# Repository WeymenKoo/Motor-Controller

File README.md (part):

# this written by claude yeh

Technical notes from a full design cycle: idea → theory → schematic → simulation → layout → fab → bring-up plan. Written as a knowledge refresher as much as a build log, so each section starts with the background needed to follow the decision.

**Status:** Rev 1 design-frozen, fabricated and partly bench-validated on a 12 V supply: MCU, gate driver (SPI), current sensing and PWM verified; a T-Motor MN601-S identified (R, L, back-EMF) and spun open-loop up to 1000 rpm. Not yet tested on the 12S bus, under load, or in closed-loop FOC. The design notes below are analytical or derived from the fabrication files.

## Repository layout

| Path | Contents |
|---|---|
| `FoC Motor Controller.kicad_pro` / `.kicad_sch` / `.kicad_pcb` | KiCad 10 project, root sheet and board |
| `Schematics/` | Hierarchical sheets (power, MCU, gate driver, MOSFETs, sensing, CAN-FD, interconnects, ...) |
| `Libraries/` | Project-local symbols, footprints and 3D models (referenced via `${KIPRJMOD}/Libraries/`) |
| `Documentation/` | Design rationale, layout/manufacturing review, board renders, RevC action summary |
| `Simulation/` | LTspice bench-correlation suite (hot-plug, half-bridge switching, current sense) with DHO804 bench captures and comparisons; see `Simulation/README.md` |
| `Project Outputs/` | BOM, pick-and-place, netlist, fabrication package (Rev 1), schematic PDF |

Open `FoC Motor Controller.kicad_pro` in KiCad 10. Vendor datasheets and the KiCad worksheet templates are not included in this repo; without the templates KiCad falls back to its default title block.

---

## 1. What and why

A single-axis field-oriented-control motor controller for one joint of a cat-scale bipedal robot. Six boards, one per joint, sharing a 12S bus, coordinated over CAN-FD.

The actuator architecture is **quasi-direct drive** — a low gear ratio (roughly 6:1 to 10:1) between a large-diameter pancake outrunner and the joint, rather than the 100:1+ of a conventional servo.

Why that matters, because it drives everything downstream:

| QDD property | Consequence for the electronics |
|---|---|
| Backdrivable, low reflected inertia | Torque control fidelity matters more than peak power. Current-sense accuracy becomes a first-class requirement, not an afterthought. |
| Joint torque ∝ motor current, almost directly | Current sense error *is* torque error. No gearbox to hide it behind. |
| Impacts transmit straight back to the motor | Regeneration is routine, not exceptional. Bus transient behaviour is a safety question. |
| It hangs on a limb | Board mass is a real constraint. An over-specified power stage is a defect, not free margin. |

Reference motor: ODrive M8325s, 100 KV, 92 mm pancake outrunner, **20 pole pairs**. That pole count comes back repeatedly.

---

## 2. Theory refresher: why FOC at all

### 2.1 The problem with six-step commutation

Trapezoidal (six-step) BLDC control energises two phases at a time and commutates on Hall transitions. It's simple, and for a fan or a drill it's fine. It has two properties that kill it for a leg joint:

- **Torque ripple.** Torque varies by roughly 13% across each 60° electrical sector because the current vector jumps in discrete steps rather than rotating smoothly.
- **No control of the current *angle*.** You can only control magnitude.

### 2.2 What FOC actually does

FOC transforms the three phase currents into a rotating reference frame locked to the rotor, so that a spinning three-phase AC problem becomes two DC quantities you can put a PI loop around.

```
Clarke:  3-phase (a,b,c)  →  2-axis stationary (α,β)
Park:    stationary (α,β) →  rotor-synchronous (d,q)   [needs rotor angle θ]

  i_d  = flux-producing current   → command 0 for a surface-PM motor
  i_q  = torque-producing current → this is your torque command
```

Two consequences worth internalising:

1. **Park needs θ.** The whole scheme collapses without an accurate rotor angle. This is why position sensing is not a peripheral feature — it is load-bearing.
2. **Commanding `i_d = 0`** means all current produces torque and none produces useless flux. That's the efficiency win over six-step, alongside the smoothness win.

The inverse path (inverse Park → SVM → gate signals) synthesises the voltage vector. **Space Vector Modulation** is worth knowing as the standard choice: it uses the two adjacent active vectors plus zero vectors, and by injecting a common-mode third harmonic it gets ~15% more bus utilisation than sinusoidal PWM for the same DC link.

### 2.3 Why sensorless was ruled out immediately

Sensorless FOC estimates θ from back-EMF. Back-EMF is proportional to speed, so at zero speed there is nothing to observe. A leg joint's primary duty is **holding position and torque at or near zero speed** — exactly where the observer has no signal.

Not a close call. Absolute magnetic encoder, AS5047P, 14-bit, over SPI.

**Refresher — magnetic encoder basics:** a diametrically-magnetised magnet on the shaft end, Hall array on the IC, sensing field *direction* not strength. Field strength only has to be in range (typically 30–70 mT). Absolute means it knows the angle at power-up with no homing move — essential when powering up a leg that is already loaded.

---

## 3. Requirements, and one I got wrong in my own documentation

```
Bus:              12S LiPo — 50.4 V full charge, 44.4 V nominal, 56 V max
Phase current:    10 A RMS continuous
Control:          sensored FOC, three-shunt low-side sensing
Comms:            CAN-FD, 6 nodes on a shared bus
Switching:        inaudible
```

### The f_sw story — worth reading as a lesson in post-hoc rationalisation

**The actual requirement was "inaudible."** 40 kHz was chosen as arbitrary headroom above the ~20 kHz audibility limit. That's it.

Later documentation in this project (including my own design record) presented a derivation:

```
f_electrical = rpm/60 × pole_pairs = 3500/60 × 20 ≈ 1167 Hz
20 PWM cycles per electrical cycle → ~23 kHz floor
∴ 40 kHz
```

That derivation is *correct arithmetic* and a genuinely useful sanity check — it confirms 40 kHz is comfortably above the control-bandwidth floor. But it is **not why the number was chosen**, and writing it up as though it were makes the design look more derived than it was.

Worth flagging because this is a common failure mode in engineering documentation: a number picked by judgement acquires a derivation after the fact, and three revisions later nobody remembers which constraint is real. If f_sw ever needs to move, the binding constraint is audibility and the charge-pump budget — not the pole-pair math.

**The 20-cycles-per-electrical-cycle rule** is still worth knowing: it's a sampling-rate argument. Your current loop runs at f_sw, and it has to track a sinusoid at f_electrical. Fewer than ~10–20 samples per cycle and the loop can't keep up with the rotating vector.

---

## 4. Design workflow

Fixed order, applied per subsystem:

```
1. First principles      → napkin numbers, identify the BINDING constraint
                           (no optimisation — the goal is order of magnitude)
2. SPICE                 → build from the napkin result, optimise here
3. Component search      → real parts, availability checked before committing
4. Power & thermal       → hot Rds(on), not the 25 °C headline
5. BoM consolidation     → once the design is stable, never during
6. Schematic review      → verify earlier action items actually landed
7. Layout
```

### Why LTspice is not used for the control loop

Tried it, abandoned it. The timescale separation is fatal:

```
Device switching:      ~5 ns edges
Mechanical settling:   ~500 ms
Ratio:                 10^8
```

A transient solver forced to resolve nanosecond edges across a mechanical settling time isn't just slow — it accumulates numerical error that swamps the result. **Control loops belong in discrete-time simulation. SPICE is for the power stage only.**

Three benches that were useful:

- `dpt_halfbridge.cir` — double-pulse test, one half-bridge
- `input_stage_transients.cir` — hot-plug and inductive transient
- `bus_regen_cascade.cir` — multi-board shared-bus regeneration

**Refresher — the double-pulse test (DPT)** is the standard method for characterising switching loss and overshoot. Two gate pulses: the first builds current in an inductive load, the gap measures turn-off, the second measures turn-on with the current already established. It isolates switching behaviour from conduction behaviour.

The single most useful result from the whole simulation effort:

```
Commutation loop inductance → V_GS undershoot
   2 nH  →  ~0 V
  80 nH  →  −4.9 V
```

Gate-oxide stress and false turn-off appear **well before** drain overshoot looks alarming on a scope. That reframed loop area as the number one layout variable, not one of several.

---

## 5. Power stage

### 5.1 Refresher: where the losses come from

```
Conduction:   P = I²_rms × R_DS(on, hot)
Switching:    P = ½ × V_bus × I × (t_r + t_f) × f_sw
```

Two things that trip people up:

**R_DS(on) roughly doubles from 25 °C to 150 °C.** The datasheet headline is at 25 °C. Using it for thermal work underestimates conduction loss by 2×.

**t_r and t_f are set by gate charge, not by the FET's "speed".** Specifically by **Q_gd**, the gate-to-drain (Miller) charge. During the Miller plateau, all your gate current goes into discharging C_gd while V_DS swings — that's the transition, and that's where switching loss happens.

```
t_r ≈ Q_gd / I_drive
```

So a "faster" FET is one with lower Q_gd, and drive current is a lever you control.

### 5.2 The 40 V mistake

Rev A used CSD18540Q5B — **40 V V_DS rating on a bus whose full-charge voltage is 50.4 V**.

Not a margin question. The device is outside its absolute maximum at rest, before anything switches.

How it happened: component selection was anchored on R_DS(on) and package, with no explicit voltage-margin gate. The rule adopted afterwards:

> **Voltage rating is checked first, against worst-case bus transient, before any other parameter is considered.**

### 5.3 The loss inversion — the most instructive result in the project

Having fixed the voltage rating, the obvious next move is the lowest R_DS(on) 100 V part available. That's how IPT015N10N5 (1.5 mΩ) entered the design.

Running the numbers at the actual operating point:

```
40 A RMS, 40 kHz, 50 V bus, I_drive = 1 A

R_DS(on)   P_cond    P_sw     P_total
1.50 mΩ    1.80 W    3.85 W   5.65 W   ← lowest Rds(on), WORST total
2.24 mΩ    2.69 W    1.58 W   4.27 W   ← best
2.70 mΩ    3.24 W    1.36 W   4.60 W
```

The 1.5 mΩ part loses because its Q_gd is 2–3× higher. **At this current and frequency, switching loss dominates conduction loss**, so the parameter everyone markets on is the wrong one to optimise.

Selection metric changed to **figure of merit**:

```
FOM = R_DS(on) × Q_g     (lower is better)
```

This is the standard metric for exactly this reason — it captures the fundamental process trade-off. A die that's bigger has lower resistance and more gate capacitance. FOM measures how good the silicon is, independent of how you sized the die.

### 5.4 Final selection

**Infineon ISC030N10NM6** (OptiMOS 6), 100 V, 3.0 mΩ max, Q_g 55 nC, Q_gd 14 nC, **PG-TDSON-8 (5 × 6 mm)**.

Note on package: earlier project notes say TOLL. The **fabricated board uses TDSON-8, the 5 × 6 mm package** — that change was made deliberately. Six TOLL packages would occupy roughly 700 mm² for a stage dissipating under a watt at the design point. On a limb, board area is mass, and mass is what the whole machine is fighting. Margin that costs nothing is worth keeping; margin that costs the primary system constraint is a defect wearing a reassuring disguise.

Sourcing note: **JLCPCB's entire 100 V TOLL inventory is optimised for 200–360 A battery/BMS applications.** Those parts buy R_DS(on) this design doesn't need by paying gate charge it can't afford (165–252 nC vs 55 nC). This is a case where local-assembly convenience had to lose to the electrical requirement, and the part became an extended/consigned line.

### 5.5 Thermal

Using hot R_DS(on) ≈ 6 mΩ, datasheet t_r/t_f of 4.5/5.3 ns, R_thJA = 50 °C/W (datasheet figure for ~6 cm² copper, no heatsinking), T_a = 40 °C:

| Phase current | P_cond (3 legs) | P_sw (6 FETs) | P per FET | T_j |
|---|---|---|---|---|
| 10 A | 1.80 W | 0.71 W | 0.42 W | 61 °C |
| 20 A | 7.20 W | 1.41 W | 1.44 W | 112 °C |

**At 10 A the inverter is thermally uncritical.** That's what makes the package downsize a real trade rather than a risk. See §11.2 for how the as-built layout changes the 20 A number.

---

## 6. Gate drive

### 6.1 Refresher: what a gate driver actually has to do

A high-side N-channel MOSFET's source sits at the switch node, which swings to the full bus voltage. To hold it on, V_GS must be ~10 V **above** the switch node — i.e. above the bus. That voltage has to come from somewhere.

Two standard approaches:

- **Bootstrap** — a capacitor charged through a diode while the low side is on. Cheap. Fails at 100% duty cycle because the cap never gets recharged.
- **Charge pump** — an on-chip doubler generating a rail above V_M continuously. Works at any duty cycle.

The DRV8323 has an integrated charge pump. That matters for FOC because SVM does spend time at very high duty on individual phases.

### 6.2 The charge pump budget — and a correction to my own analysis

The charge pump supplies the **high-side** gates only (low-side gates are driven from an internal linear regulator off V_M). TI's datasheet gives:

```
I_VCP ≥ 3 × Q_g × f_PWM        [3 high-side gates]
```

At 55 nC and 40 kHz:

```
I_required = 3 × 55 nC × 40 kHz = 6.6 mA
I_available = 25 mA
Margin = 3.8×                                 ✓ comfortable

Q_g ceiling at 2× margin = 25 mA / (2 × 3 × 40 kHz) ≈ 104 nC
```

**Correction to earlier project documentation.** A design record I wrote during this project claimed the correct 2×-margin ceiling was ~52 nC, derived from `6 × Q_g × f_sw` — counting all six devices. That is wrong: the low-side gates are not a charge-pump load. The original project note (~100 nC at 2× margin) was right and my "correction" introduced an error.

The lesson generalises: **when you re-derive someone's number and get a different answer, check whether you changed the model before concluding they were wrong.** A factor-of-two disagreement is usually a definition disagreement, not an arithmetic one.

Separately, the capability figure itself was corrected in the other direction: an early note said the charge pump supplies 10–15 mA. That's the low-V_M figure where the doubler is strained. At a 44–50 V bus it's **25 mA**.

### 6.3 Slew rate control: gate side, not drain side

**Refresher on the trade.** Fast switching = low switching loss, but high dv/dt and di/dt, which means more overshoot (`V = L·di/dt` across the commutation loop inductance) and more EMI. Slow switching is the opposite. You need a knob.

Three ways to get one:

| Approach | How it works | Verdict here |
|---|---|---|
| Drain-source RC snubber | Damps the loop-L / C_oss resonance | Rejected — costs board area, burns power continuously, and needs resistor power-rating work |
| Asymmetric gate network (R + parallel diode) | Slow turn-on, fast turn-off | Rejected — this is a workaround for drivers with a single fixed drive current |
| Programmable I_DRIVE | Driver sources/sinks a configured current | **Selected** |

The DRV8323's Smart Gate Drive provides independently programmable source and sink currents over SPI — the same asymmetry the diode network provides, implemented internally. TI's own app note recommends a single small or 0 Ω external series resistor when it's in use.

Sizing:

```
I_DRIVE = Q_gd / t_r_target = 14 nC / 50 ns = 280 mA
```

Shipped configuration: **0 Ω series gate resistors populated** (so I_DRIVE has sole control), with the gate-source RC network (3.9 Ω + 2.2 nF per FET) **fitted as DNP footprints**. That's deliberate insurance — ship with the simplest arrangement, add damping only if the real waveforms demand it.

One thing to know if you populate them: a 2.2 nF gate-source cap adds ~22 nC per device to the charge-pump demand (`Q = C·V`). Re-check the budget before doing it.

**Honest caveat:** this replaced a *sized* snubber with a *removed* snubber. That converts a sizing task into a validation task, and it raises rather than lowers the priority of the DPT work. The board has no drain-side snubber footprints, which in hindsight should have been added as DNP.

### 6.4 Dead time

**Refresher:** both FETs in a leg on simultaneously = shoot-through = a direct short across the bus through two devices. Dead time is the deliberate gap where both are off.

```
t_dead > t_r + t_f + driver propagation delay mismatch
```

Start conservative (200–300 ns), measure, reduce. It's SPI-programmable, so it's a bench task, not a design-time commitment. Note that the datasheet's 4.5/5.3 ns figures are quoted at R_g = 1.6 Ω, which is *not* this gate network.

---

## 7. Current sensing

### 7.1 Refresher: the three topologies

| Topology | Pros | Cons |
|---|---|---|
| **Low-side shunt** | Ground-referenced, cheap, simple amplifier | Blind at very high duty cycle; measures leg current not phase current |
| **In-line phase** | True phase current at any duty | Needs high-common-mode or isolated amps; expensive |
| **High-side** | Sees bus current | Common mode at bus voltage |

Chose **three low-side shunts** into the DRV8323's integrated CSAs. Three rather than two: the third gives redundancy and a consistency check (`i_a + i_b + i_c = 0`) rather than requiring reconstruction.

### 7.2 The thing that actually determines whether it works

Not the filter. **Sample timing.**

Low-side shunt current is only valid while the low-side FET is on. During switching transients it's garbage. The fix is to sample at the **centre of the PWM period**, where all three low sides are on and the transients have settled:

```
Centre-aligned PWM → TIM1_TRGO2 at the counter peak → triggers ADC
```

The RC filter on the sense lines (56 Ω + 2.2 nF, f_c ≈ 1.29 MHz, τ ≈ 123 ns) is **edge damping and ADC input protection, not switching-noise rejection**. At 40 kHz it attenuates nothing. Its job is to be settled by the time the sample fires — 10τ ≈ 1.23 µs of margin.

> Filtering cannot substitute for correct sample timing. If your currents are noisy proportional to duty cycle, move the trigger; don't add capacitance.

### 7.3 Shunt and gain are one decision

```
Full scale = (V_ref / 2) / (G × R_shunt)

3 mΩ, G=20  →  ±27.5 A    ✓ selected
3 mΩ, G=40  →  ±13.75 A   ✗ below peak current
5 mΩ, G=20  →  ±16.5 A    ✗ only 1.17× over the 14.1 A peak
5 mΩ, G=10  →  ±33 A      — the earlier frozen value
```

Resolution at the shipped config: **~13.4 mA/LSB**. Dissipation: 0.3 W each at 10 A, 1.2 W at 20 A, in a 3 W part.

**Refresher — Kelvin sensing.** A 3 mΩ shunt develops 30 mV at 10 A. A few mΩ of trace or solder-joint resistance in the sense path is a large fraction of that. Kelvin (4-wire) connection taps the sense voltage at the resistor body itself, carrying no power current. Implemented here with net ties on the sense pads.

### 7.4 A retracted instruction worth recording

An action item carried forward for several revisions said: **change the shunts from 5 mΩ to 1 mΩ, critical.**

It was generated during a MOSFET-selection exercise at a **40 A RMS** operating point, where 5 mΩ would dissipate 8 W in a 3 W part. Entirely correct there.

At the frozen 10 A design point it's unnecessary and actively harmful — it throws away a factor of five in sense resolution for no thermal benefit.

> **An action item carried forward without its operating-point context is worse than no action item.** Every carried item should state the assumption it depends on.

### 7.5 Overcurrent protection: know what's actually protecting you

Two mechanisms exist on the DRV8323:

- **SEN_OCP** — threshold across the sense resistor. At 3 mΩ this implies a trip current in the hundreds of amps. **Unusable.**
- **VDS_OCP** — measures V_DS across the conducting FET.

```
VDS_LVL = I_trip × R_DS(on, hot)
        = 20 A × 6 mΩ = 120 mV
```

Even configured well, hardware OCP sits far above the working range (on the order of 80 A+ against ~10 A operation). The practical consequence:

> **In normal operation, firmware current limiting is the only real protection.** Hardware OCP is a catastrophe backstop — shorted phase, shorted FET — not a current limit. The firmware limit must be robust, because nothing underneath it will catch a 15 A overcurrent.

---

## 8. Power tree, and a scope decision

### 8.1 The cut that mattered most

Early revisions carried a full input-protection front end on the controller board: LM5069 hot-swap controller, back-to-back SOA-rated pass FETs, inrush limiting, UVLO/OVLO, current limit, latch-off.

**That was removed.** Input protection and hot-swap are delegated to a dedicated upstream **Power Distribution Board (PDB)**, shared across all six joints.

This is the right architectural call and it's worth stating why:

- Hot-swap protection is a **bus-level** function. Six copies of it is six times the mass and cost for a job that only needs doing once, at the point where the bus meets the battery.
- The hardest constraints (SOA-rated pass FETs, inrush energy into 500 µF, latch-reset access) get easier when there's one of them in an accessible place instead of six buried in limb segments.
- It removed roughly a dozen line items and a significant chunk of board area from every joint.

Alongside it, the board also runs **bench-powered** during lab work — which is the correct way to bring up a prototype anyway.

What stayed on-board: a local TVS clamp (SMCJ51CA). Local transient clamping is still a board-level responsibility.

### 8.2 The remaining power tree

```
+VPROT (36–56 V) → LMR36520 buck (400 kHz) → +5 V
                                            → TLV75733 LDO → +3V3
```

Two converters. Simple, and defensible: a single-stage 50 V → 3.3 V buck runs at a tiny duty cycle with poor transient behaviour, and the 5 V rail is needed anyway for the CAN transceiver and connector supply pins.

### 8.3 The pre-boot window

**Refresher on why this matters more than power-up ordering.** No sequence of rails coming up will destroy anything here. What sequencing actually buys you is the guarantee that **the gate driver is never live and armed while the MCU's PWM state is undefined**.

+VPROT is live for tens of milliseconds before the MCU boots. During that window:

```
REQUIRED: external 10 kΩ pulldowns on DRV_ENABLE, DRV_CAL,
          and all six INHx/INLx.
```

The driver's internal 100 kΩ pulldowns are too weak to rely on against flux residue, probing, or partial population. A floating CAL pin can put the amplifiers into calibration mode at power-up.

Also: `nFAULT` and `nSCS` pull-ups must go to the **main 3.3 V rail**, never to the driver's own generated DVDD — which dies whenever the driver is disabled, exactly when you most want to read the fault line.

### 8.4 Power-down ordering works in your favour

```
DRV8323 V_M UVLO ≈ 6 V
Buck operates down to a much lower input
```

On bus collapse, **gate drive dies before logic does**. That window is what lets the MCU log the fault and emit a CAN frame. Put fault reporting early in the brown-out handler and you get a free post-mortem.

### 8.5 An open finding: no separate analog rail

In the fabricated Rev 1, **VDDA, VREF+ and the DRV8323 VREF all sit on the raw +3V3 digital rail.**

**Refresher on why that's not ideal.** The ADC reference sets the absolute scale of every measurement. A 12-bit converter on a 3.3 V reference has 1 LSB = 806 µV. An LDO gives maybe 40 dB of rejection at 100 kHz and only 10–20 dB by 1 MHz, so switching ripple reaching the rail translates directly into reference wander — ~10 mV of ripple is ~12 LSB, more than the converter's own unadjusted error budget.

Rev 2 fix: ferrite bead plus local caps to create a separate `+3V3A` node.

Partial mitigation that already exists: **current sense is ratiometric** through the DRV8323's own VREF, so CSA gain error largely cancels. Bus voltage and temperature sensing are *not* ratiometric and inherit the LDO's absolute accuracy directly.

---

## 9. Communications

### 9.1 CAN-FD

Convergent choice across every comparable open-source design (ODrive, moteus). Deterministic multi-drop on a six-node bus, enough payload for command + telemetry, two-wire harness that suits a limb.

**Refresher — split termination.** Standard CAN termination is 120 Ω across the pair at each end of the bus. *Split* termination divides it into 2 × 60.4 Ω with a capacitor (47 nF here) from the midpoint to ground. The differential impedance is unchanged; the capacitor gives common-mode energy somewhere to go.

```
Common-mode path: 30.2 Ω × 47 nF → f_c ≈ 112 kHz
```

**Termination topology is a system-level property, not a board property:**

```
6 nodes, each with 120 Ω fitted  →  20 Ω bus  →  does not work
Correct: exactly 2 terminators, at the two PHYSICAL ends
```

So termination must be selectable per board while keeping every board identical. On this layout the split network (R45/R46/C68) sits clustered with **SW1**, a DPDT slide switch — a DPDT being exactly what you need to bring both lines into termination.

### 9.2 Oscillator tolerance — the constraint people miss

**Refresher.** CAN has no separate clock line. Receivers resynchronise on edges, and the tolerance budget has to accommodate *both* nodes' clock error. CAN-FD's data phase is faster and the budget is correspondingly tighter.

```
Ceramic resonator:  ±0.5%  = ±5000 ppm
Quartz crystal:     ±30 ppm typical
Ratio:              ~170×
```

A ceramic resonator is marginal for classical CAN and generally insufficient for CAN-FD data-phase bit timing. Swapped to quartz. Cost: about 35 cents and two load capacitors.

There was no competing constraint because native USB was dropped (see §10), so the crystal only serves the timer and CAN clock trees.

### 9.3 Node addressing — an idea that came and went

Six physically identical boards need to be distinguishable **without reflashing**, and a board swapped in the field should take on the identity of the joint it's installed in. So the ID must be in hardware.

**Approach 1 — binary-weighted resistor ladder into one ADC pin.** Four jumpers, 16 addresses, one pin instead of four GPIO.

```
V_node = 3.3 / (1 + n)      where n = binary sum of closed jumpers

code 0  → 3.300 V
code 1  → 1.650 V
code 7  → 0.413 V
code 15 → 0.206 V
```

Two engineering notes on this that are generally useful:

- **The response compresses at high codes.** Gap between codes 14 and 15 is ~13.75 mV. That forces 1% resistors, oversampling, and a boot-time-only read — all required, not optional.
- **Source impedance hits 100 kΩ at code 0**, which demands the maximum ADC sampling time. Fine, because it's read once before PWM is active, so switching noise is absent entirely.

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
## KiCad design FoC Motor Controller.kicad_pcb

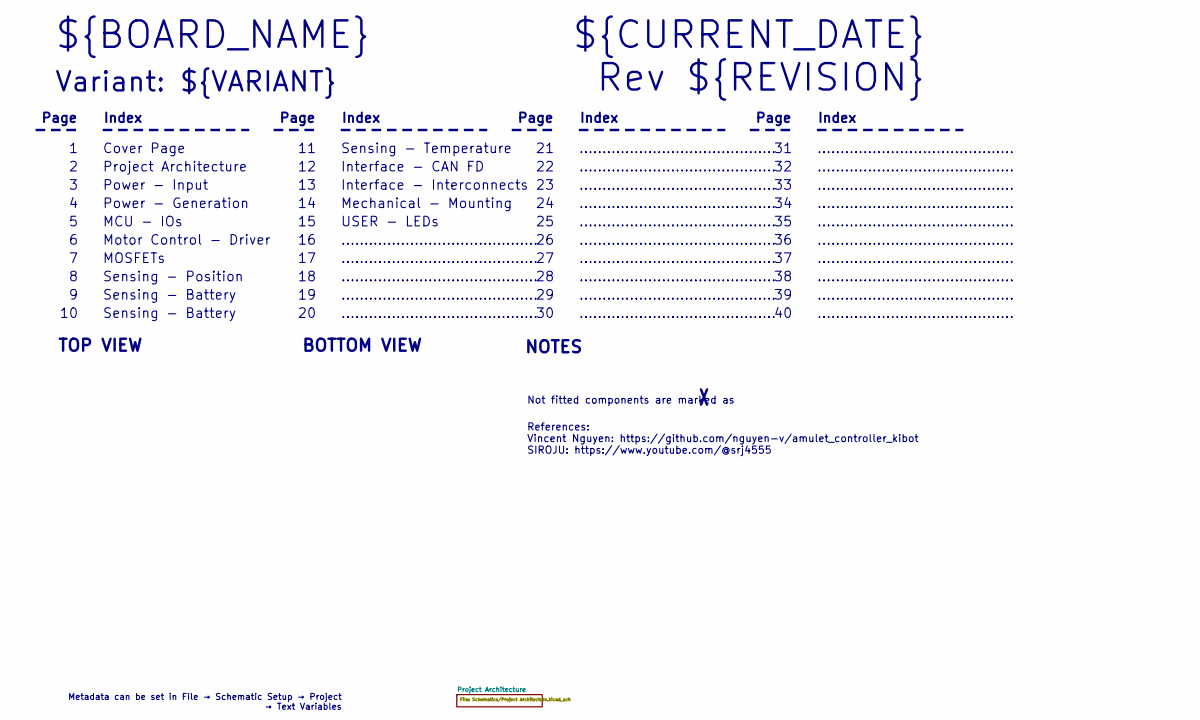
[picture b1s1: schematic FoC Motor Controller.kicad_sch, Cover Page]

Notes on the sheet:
BOTTOM VIEW
...........................................
Page
TOP VIEW
Sensing - Battery
Sensing - Position
Not fitted components are marked as
Index
Interface - Interconnects
Power - Generation
${CURRENT_DATE}
Variant: ${VARIANT}
Rev ${REVISION}
MCU - IOs
Sensing - Temperature
USER - LEDs
${BOARD_NAME}
Mechanical - Mounting
Motor Control - Driver
Project Architecture
References: Vincent Nguyen: https://github.com/nguyen-v/amulet_controller_kibot SIROJU: https://www.youtube.com/@srj4555
Cover Page
NOTES
Interface - CAN FD
Power - Input
MOSFETs
Metadata can be set in File → Schematic Setup → Project → Text Variables

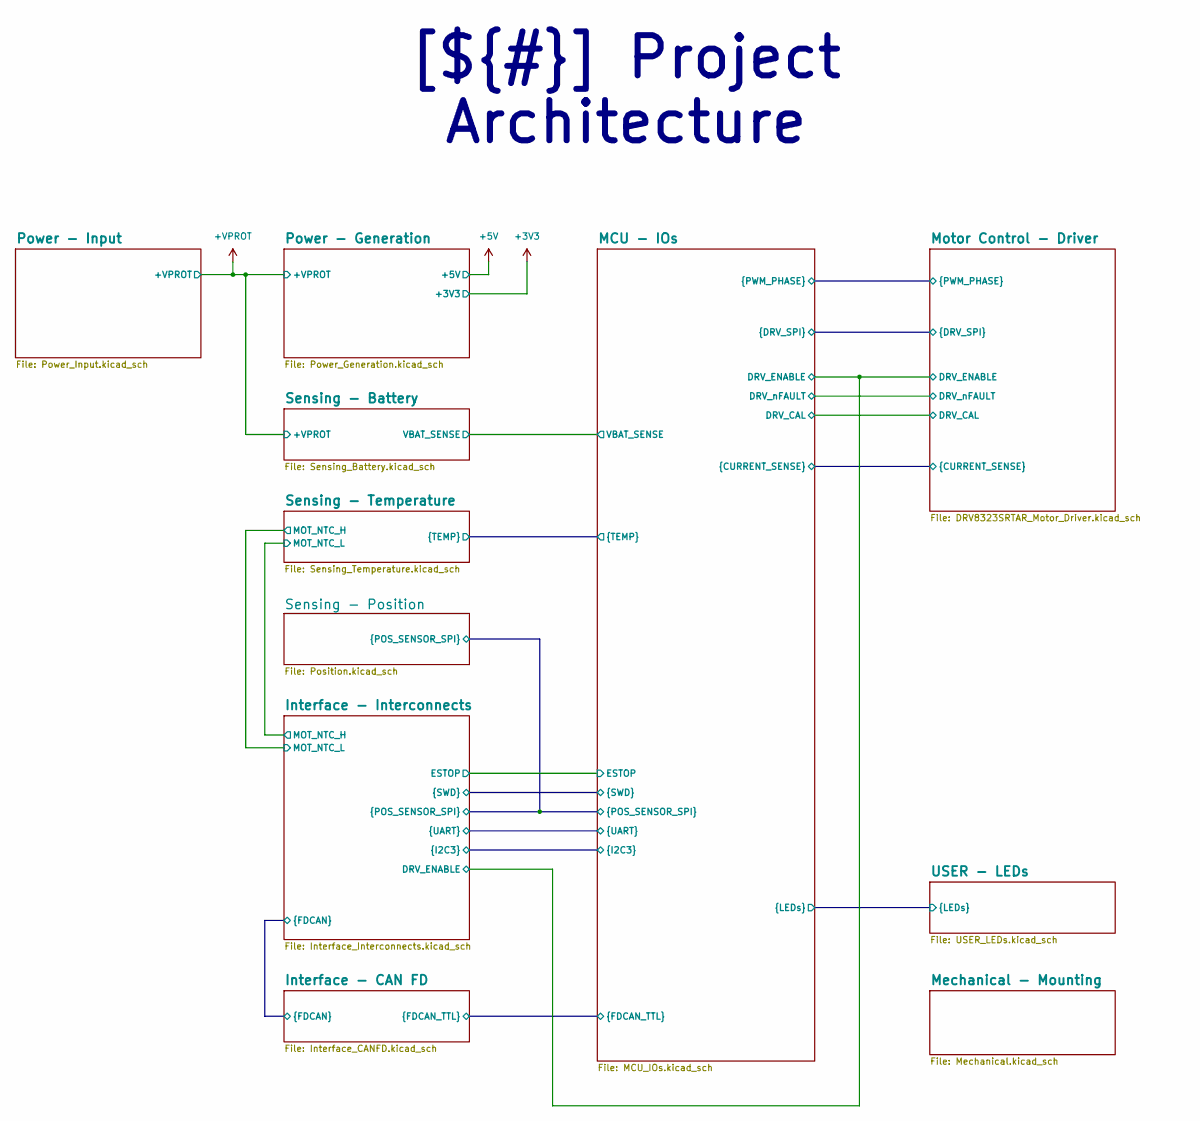
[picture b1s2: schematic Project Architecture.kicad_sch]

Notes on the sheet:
[${#}] ${TITLE}

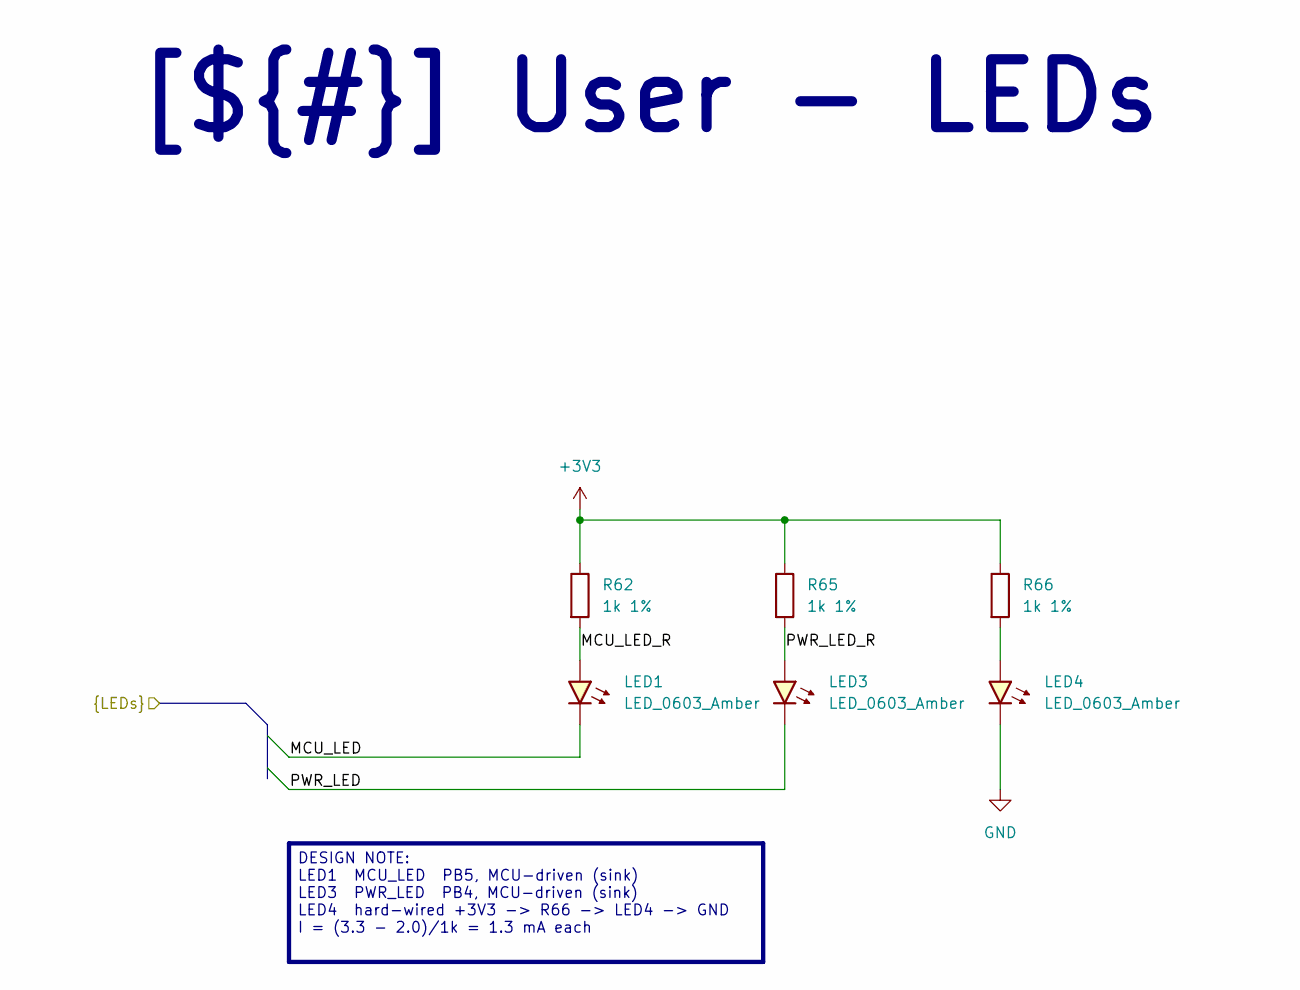
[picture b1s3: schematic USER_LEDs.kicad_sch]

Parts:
LED1, LED3, LED4: LED_0603_Amber; LED_0603_1608Metric
R62, R65, R66: 1k 1%; R_0402_1005Metric

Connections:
+3V3: R62.1, R65.1, R66.1; also elsewhere on the board
/Project Architecture/MCU - IOs/MCU_LED: LED1.1 (K); also elsewhere on the board
/Project Architecture/MCU - IOs/PWR_LED: LED3.1 (K); also elsewhere on the board
/Project Architecture/USER - LEDs/MCU_LED_R: LED1.2 (A), R62.2
/Project Architecture/USER - LEDs/PWR_LED_R: LED3.2 (A), R65.2
GND: LED4.1 (K); also elsewhere on the board
unnamed: LED4.2 (A), R66.2

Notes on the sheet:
[${#}] User - LEDs
DESIGN NOTE: LED1 MCU_LED PB5, MCU-driven (sink) LED3 PWR_LED PB4, MCU-driven (sink) LED4 hard-wired +3V3 -> R66 -> LED4 -> GND I = (3.3 - 2.0)/1k = 1.3 mA each

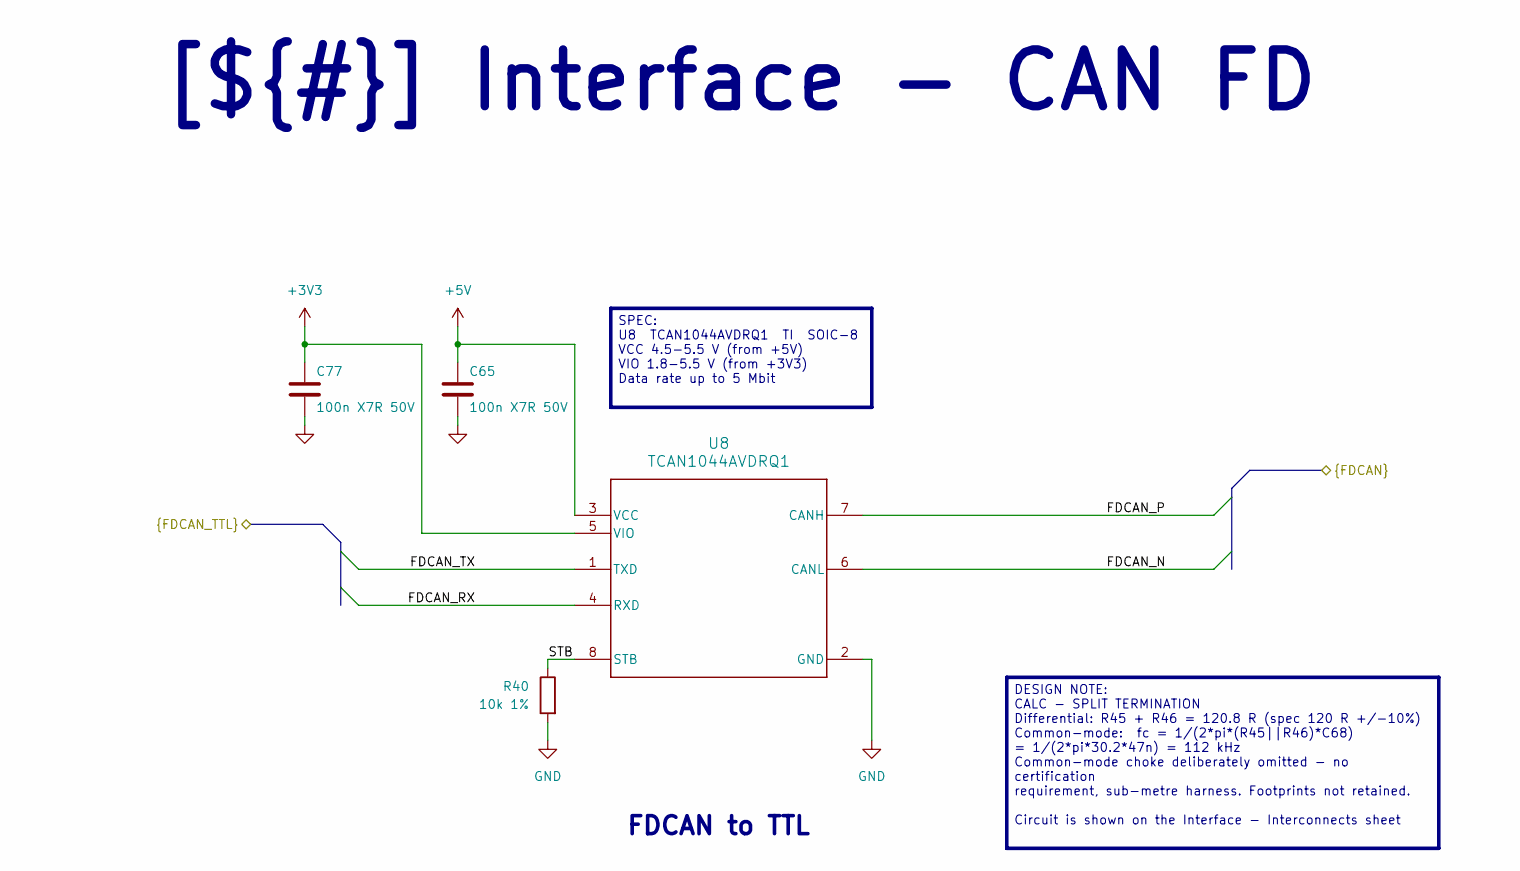
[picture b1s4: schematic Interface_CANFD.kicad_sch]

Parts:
C65, C77: 100n X7R 50V; C_0402_1005Metric
R40: 10k 1%; R_0402_1005Metric
U8: TCAN1044AVDRQ1; D0008A-IPC_A

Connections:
+3V3: C77.1, U8.5 (VIO); also elsewhere on the board
+5V: C65.1, U8.3 (VCC); also elsewhere on the board
/Project Architecture/Interface - CAN FD/FDCAN_N: U8.6 (CANL); also elsewhere on the board
/Project Architecture/Interface - CAN FD/FDCAN_P: U8.7 (CANH); also elsewhere on the board
/Project Architecture/Interface - CAN FD/FDCAN_RX: U8.4 (RXD); also elsewhere on the board
/Project Architecture/Interface - CAN FD/FDCAN_TX: U8.1 (TXD); also elsewhere on the board
/Project Architecture/Interface - CAN FD/STB: R40.1, U8.8 (STB)
GND: C65.2, C77.2, R40.2, U8.2 (GND); also elsewhere on the board

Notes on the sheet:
[${#}] Interface - CAN FD
FDCAN to TTL
DESIGN NOTE: CALC - SPLIT TERMINATION Differential: R45 + R46 = 120.8 R (spec 120 R +/-10%) Common-mode: fc = 1/(2*pi*(R45||R46)*C68) = 1/(2*pi*30.2*47n) = 112 kHz Common-mode choke deliberately omitted - no certification requirement, sub-metre harness. Footprints not retained. Circuit is shown on 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
SPEC: U8 TCAN1044AVDRQ1 TI SOIC-8 VCC 4.5-5.5 V (from +5V) VIO 1.8-5.5 V (from +3V3) Data rate up to 5 Mbit

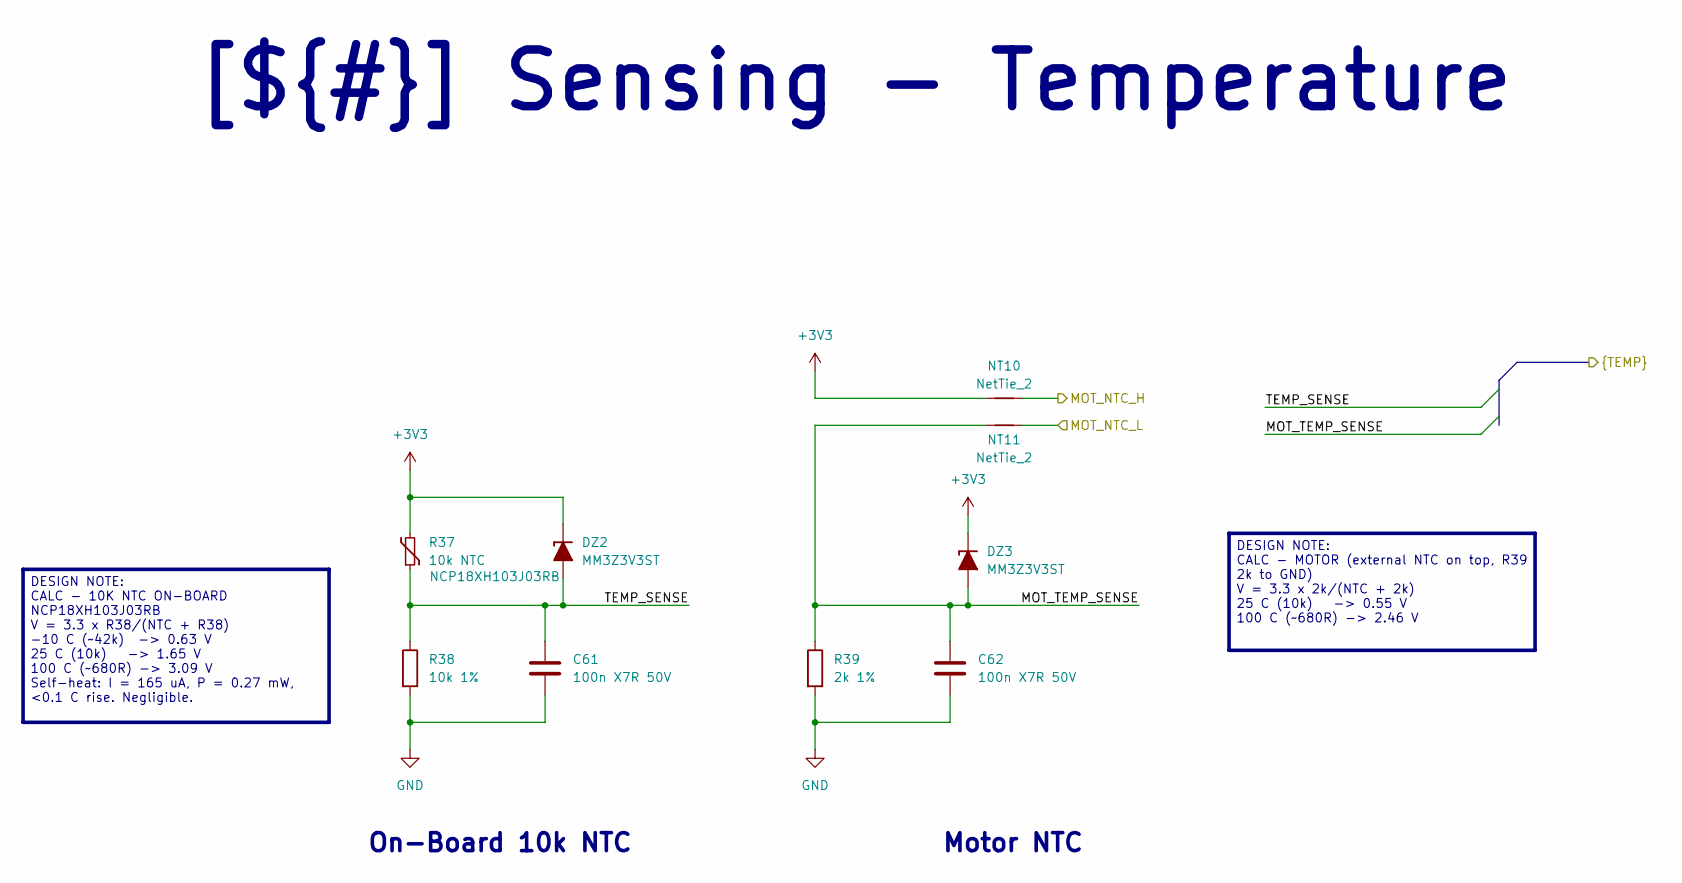
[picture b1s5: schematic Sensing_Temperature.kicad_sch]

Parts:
C61, C62: 100n X7R 50V; C_0402_1005Metric
DZ2, DZ3: MM3Z3V3ST; D_SOD-323
NT10, NT11: NetTie_2; NetTie-2_SMD_Pad0.5mm
R37: 10k NTC; R_0603_1608Metric; ManufacturerPartNumber NCP18XH103J03RB
R38: 10k 1%; R_0402_1005Metric
R39: 2k 1%; R_0402_1005Metric

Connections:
+3V3: DZ2.1 (K), DZ3.1 (K), NT10.1, R37.2; also elsewhere on the board
/Project Architecture/Interface - Interconnects/MOT_NTC_H: NT11.2; also elsewhere on the board
/Project Architecture/Interface - Interconnects/MOT_NTC_L: NT10.2; also elsewhere on the board
/Project Architecture/MCU - IOs/MOT_TEMP_SENSE: C62.1, DZ3.2 (A), NT11.1, R39.1; also elsewhere on the board
/Project Architecture/MCU - IOs/TEMP_SENSE: C61.1, DZ2.2 (A), R37.1, R38.1; also elsewhere on the board
GND: C61.2, C62.2, R38.2, R39.2; also elsewhere on the board

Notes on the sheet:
[${#}] Sensing - Temperature
On-Board 10k NTC
DESIGN NOTE: CALC - 10K NTC ON-BOARD NCP18XH103J03RB V = 3.3 x R38/(NTC + R38) -10 C (~42k) -> 0.63 V 25 C (10k) -> 1.65 V 100 C (~680R) -> 3.09 V Self-heat: I = 165 uA, P = 0.27 mW, <0.1 C rise. Negligible.
Motor NTC
DESIGN NOTE: CALC - MOTOR (external NTC on top, R39 2k to GND) V = 3.3 x 2k/(NTC + 2k) 25 C (10k) -> 0.55 V 100 C (~680R) -> 2.46 V

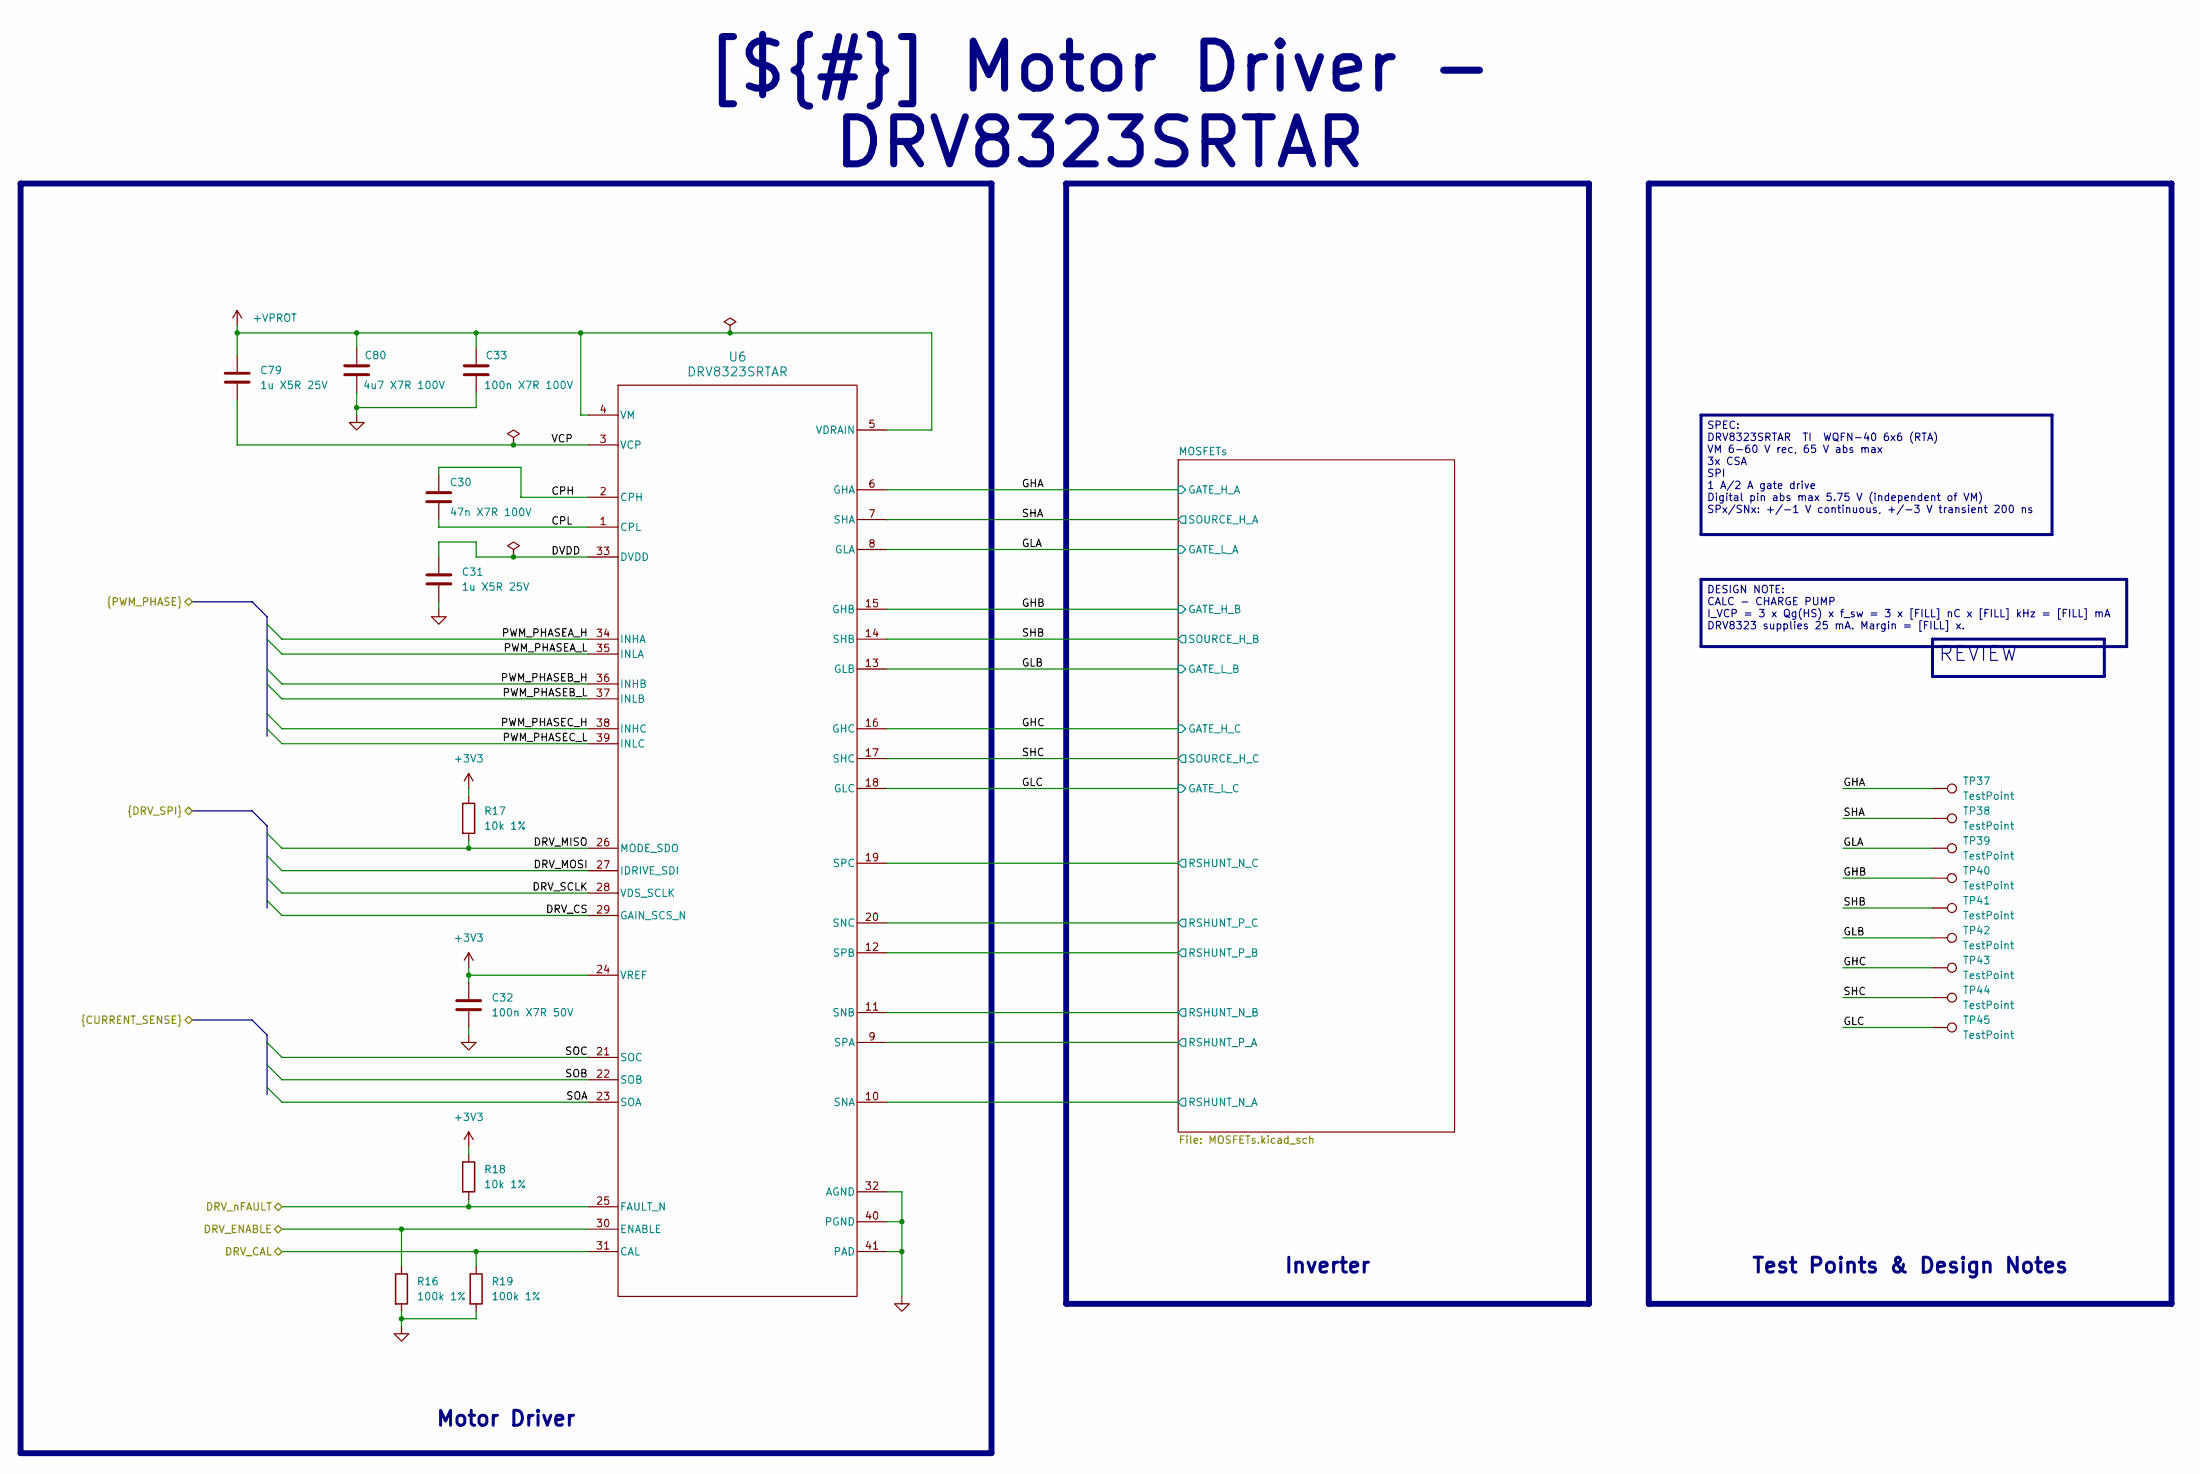
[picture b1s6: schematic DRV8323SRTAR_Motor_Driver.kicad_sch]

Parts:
C30: 47n X7R 100V; C_0603_1608Metric_Pad1.08x0.95mm_HandSolder
C31, C79: 1u X5R 25V; C_0603_1608Metric
C32: 100n X7R 50V; C_0402_1005Metric
C33: 100n X7R 100V; C_0603_1608Metric_Pad1.08x0.95mm_HandSolder
C80: 4u7 X7R 100V; C_1210_3225Metric_Pad1.33x2.70mm_HandSolder
R16, R19: 100k 1%; R_0402_1005Metric
R17, R18: 10k 1%; R_0402_1005Metric
TP37, TP38, TP39, TP40, TP41, TP42, TP43, TP44, TP45: TestPoint; TestPoint-0.5mm
U6: DRV8323SRTAR; RTA0040B

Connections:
+3V3: C32.1, R17.1, R18.1, U6.24 (VREF); also elsewhere on the board
+VPROT: C33.1, C79.1, C80.1, U6.4 (VM), U6.5 (VDRAIN); also elsewhere on the board
/Project Architecture/MCU - IOs/DRV_CAL: R19.1, U6.31 (CAL); also elsewhere on the board
/Project Architecture/MCU - IOs/DRV_CS: U6.29 (GAIN_SCS_N); also elsewhere on the board
/Project Architecture/MCU - IOs/DRV_ENABLE: R16.1, U6.30 (ENABLE); also elsewhere on the board
/Project Architecture/MCU - IOs/DRV_MISO: R17.2, U6.26 (MODE_SDO); also elsewhere on the board
/Project Architecture/MCU - IOs/DRV_MOSI: U6.27 (IDRIVE_SDI); also elsewhere on the board
/Project Architecture/MCU - IOs/DRV_SCLK: U6.28 (VDS_SCLK); also elsewhere on the board
/Project Architecture/MCU - IOs/DRV_nFAULT: R18.2, U6.25 (FAULT_N); also elsewhere on the board
/Project Architecture/MCU - IOs/PWM_PHASEA_H: U6.34 (INHA); also elsewhere on the board
/Project Architecture/MCU - IOs/PWM_PHASEA_L: U6.35 (INLA); also elsewhere on the board
/Project Architecture/MCU - IOs/PWM_PHASEB_H: U6.36 (INHB); also elsewhere on the board
/Project Architecture/MCU - IOs/PWM_PHASEB_L: U6.37 (INLB); also elsewhere on the board
/Project Architecture/MCU - IOs/PWM_PHASEC_H: U6.38 (INHC); also elsewhere on the board
/Project Architecture/MCU - IOs/PWM_PHASEC_L: U6.39 (INLC); also elsewhere on the board
/Project Architecture/MCU - IOs/SOA: U6.23 (SOA); also elsewhere on the board
/Project Architecture/MCU - IOs/SOB: U6.22 (SOB); also elsewhere on the board
/Project Architecture/MCU - IOs/SOC: U6.21 (SOC); also elsewhere on the board
/Project Architecture/Motor Control - Driver/CPH: C30.1, U6.2 (CPH)
/Project Architecture/Motor Control - Driver/CPL: C30.2, U6.1 (CPL)
/Project Architecture/Motor Control - Driver/DVDD: C31.1, U6.33 (DVDD)
/Project Architecture/Motor Control - Driver/GHA: TP37.1 (1_1), U6.6 (GHA); also elsewhere on the board
/Project Architecture/Motor Control - Driver/GHB: TP40.1 (1_1), U6.15 (GHB); also elsewhere on the board
/Project Architecture/Motor Control - Driver/GHC: TP43.1 (1_1), U6.16 (GHC); also elsewhere on the board
/Project Architecture/Motor Control - Driver/GLA: TP39.1 (1_1), U6.8 (GLA); also elsewhere on the board
/Project Architecture/Motor Control - Driver/GLB: TP42.1 (1_1), U6.13 (GLB); also elsewhere on the board
/Project Architecture/Motor Control - Driver/GLC: TP45.1 (1_1), U6.18 (GLC); also elsewhere on the board
/Project Architecture/Motor Control - Driver/MOSFETs/RSHUNT_N_A: U6.10 (SNA); also elsewhere on the board
/Project Architecture/Motor Control - Driver/MOSFETs/RSHUNT_N_B: U6.11 (SNB); also elsewhere on the board
/Project Architecture/Motor Control - Driver/MOSFETs/RSHUNT_N_C: U6.19 (SPC); also elsewhere on the board
/Project Architecture/Motor Control - Driver/MOSFETs/RSHUNT_P_A: U6.9 (SPA); also elsewhere on the board
/Project Architecture/Motor Control - Driver/MOSFETs/RSHUNT_P_B: U6.12 (SPB); also elsewhere on the board
/Project Architecture/Motor Control - Driver/MOSFETs/RSHUNT_P_C: U6.20 (SNC); also elsewhere on the board
/Project Architecture/Motor Control - Driver/SHA: TP38.1 (1_1), U6.7 (SHA); also elsewhere on the board
/Project Architecture/Motor Control - Driver/SHB: TP41.1 (1_1), U6.14 (SHB); also elsewhere on the board
/Project Architecture/Motor Control - Driver/SHC: TP44.1 (1_1), U6.17 (SHC); also elsewhere on the board
/Project Architecture/Motor Control - Driver/VCP: C79.2, U6.3 (VCP)
GND: C31.2, C32.2, C33.2, C80.2, R16.2, R19.2, U6.32 (AGND), U6.40 (PGND), U6.41 (PAD); also elsewhere on the board

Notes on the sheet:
REVIEW
SPEC: DRV8323SRTAR TI WQFN-40 6x6 (RTA) VM 6-60 V rec, 65 V abs max 3x CSA SPI 1 A/2 A gate drive Digital pin abs max 5.75 V (independent of VM) SPx/SNx: +/-1 V continuous, +/-3 V transient 200 ns
DESIGN NOTE: CALC - CHARGE PUMP I_VCP = 3 x Qg(HS) x f_sw = 3 x [FILL] nC x [FILL] kHz = [FILL] mA DRV8323 supplies 25 mA. Margin = [FILL] x.
Motor Driver
Inverter
[${#}] Motor Driver - DRV8323SRTAR
Test Points & Design Notes

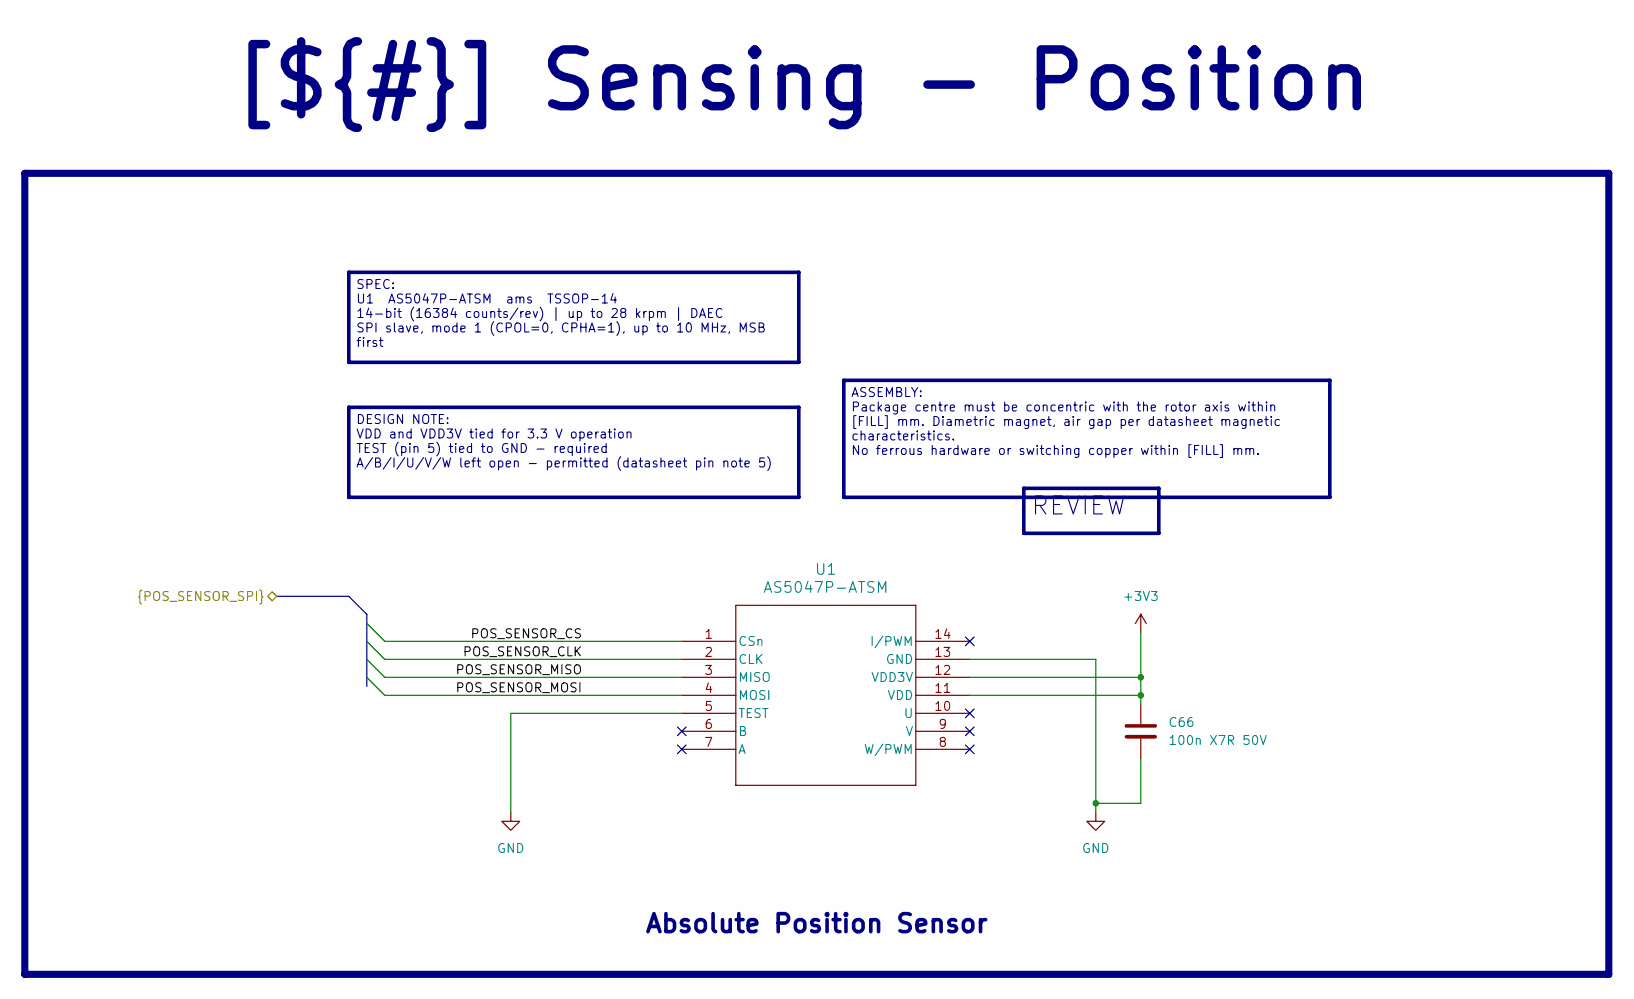
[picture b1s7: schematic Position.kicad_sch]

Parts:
C66: 100n X7R 50V; C_0402_1005Metric
U1: AS5047P-ATSM; TSSOP14_OSM

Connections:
+3V3: C66.1, U1.11 (VDD), U1.12 (VDD3V); also elsewhere on the board
/Project Architecture/Interface - Interconnects/POS_SENSOR_CLK: U1.2 (CLK); also elsewhere on the board
/Project Architecture/Interface - Interconnects/POS_SENSOR_CS: U1.1 (CSn); also elsewhere on the board
/Project Architecture/Interface - Interconnects/POS_SENSOR_MISO: U1.3 (MISO); also elsewhere on the board
/Project Architecture/Interface - Interconnects/POS_SENSOR_MOSI: U1.4 (MOSI); also elsewhere on the board
GND: C66.2, U1.5 (TEST), U1.13 (GND); also elsewhere on the board

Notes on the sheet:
[${#}] Sensing - Position
Absolute Position Sensor
SPEC: U1 AS5047P-ATSM ams TSSOP-14 14-bit (16384 counts/rev) | up to 28 krpm | DAEC SPI slave, mode 1 (CPOL=0, CPHA=1), up to 10 MHz, MSB first
ASSEMBLY: Package centre must be concentric with the rotor axis within [FILL] mm. Diametric magnet, air gap per datasheet magnetic characteristics. No ferrous hardware or switching copper within [FILL] mm.
DESIGN NOTE: VDD and VDD3V tied for 3.3 V operation TEST (pin 5) tied to GND - required A/B/I/U/V/W left open - permitted (datasheet pin note 5)
REVIEW
